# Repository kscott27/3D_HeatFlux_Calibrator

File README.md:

# 3D_HeatFlux_Calibrator
Firmware, GUI, and electronic circuit board files for a 3-dimensional, automated heat flux calibrator.

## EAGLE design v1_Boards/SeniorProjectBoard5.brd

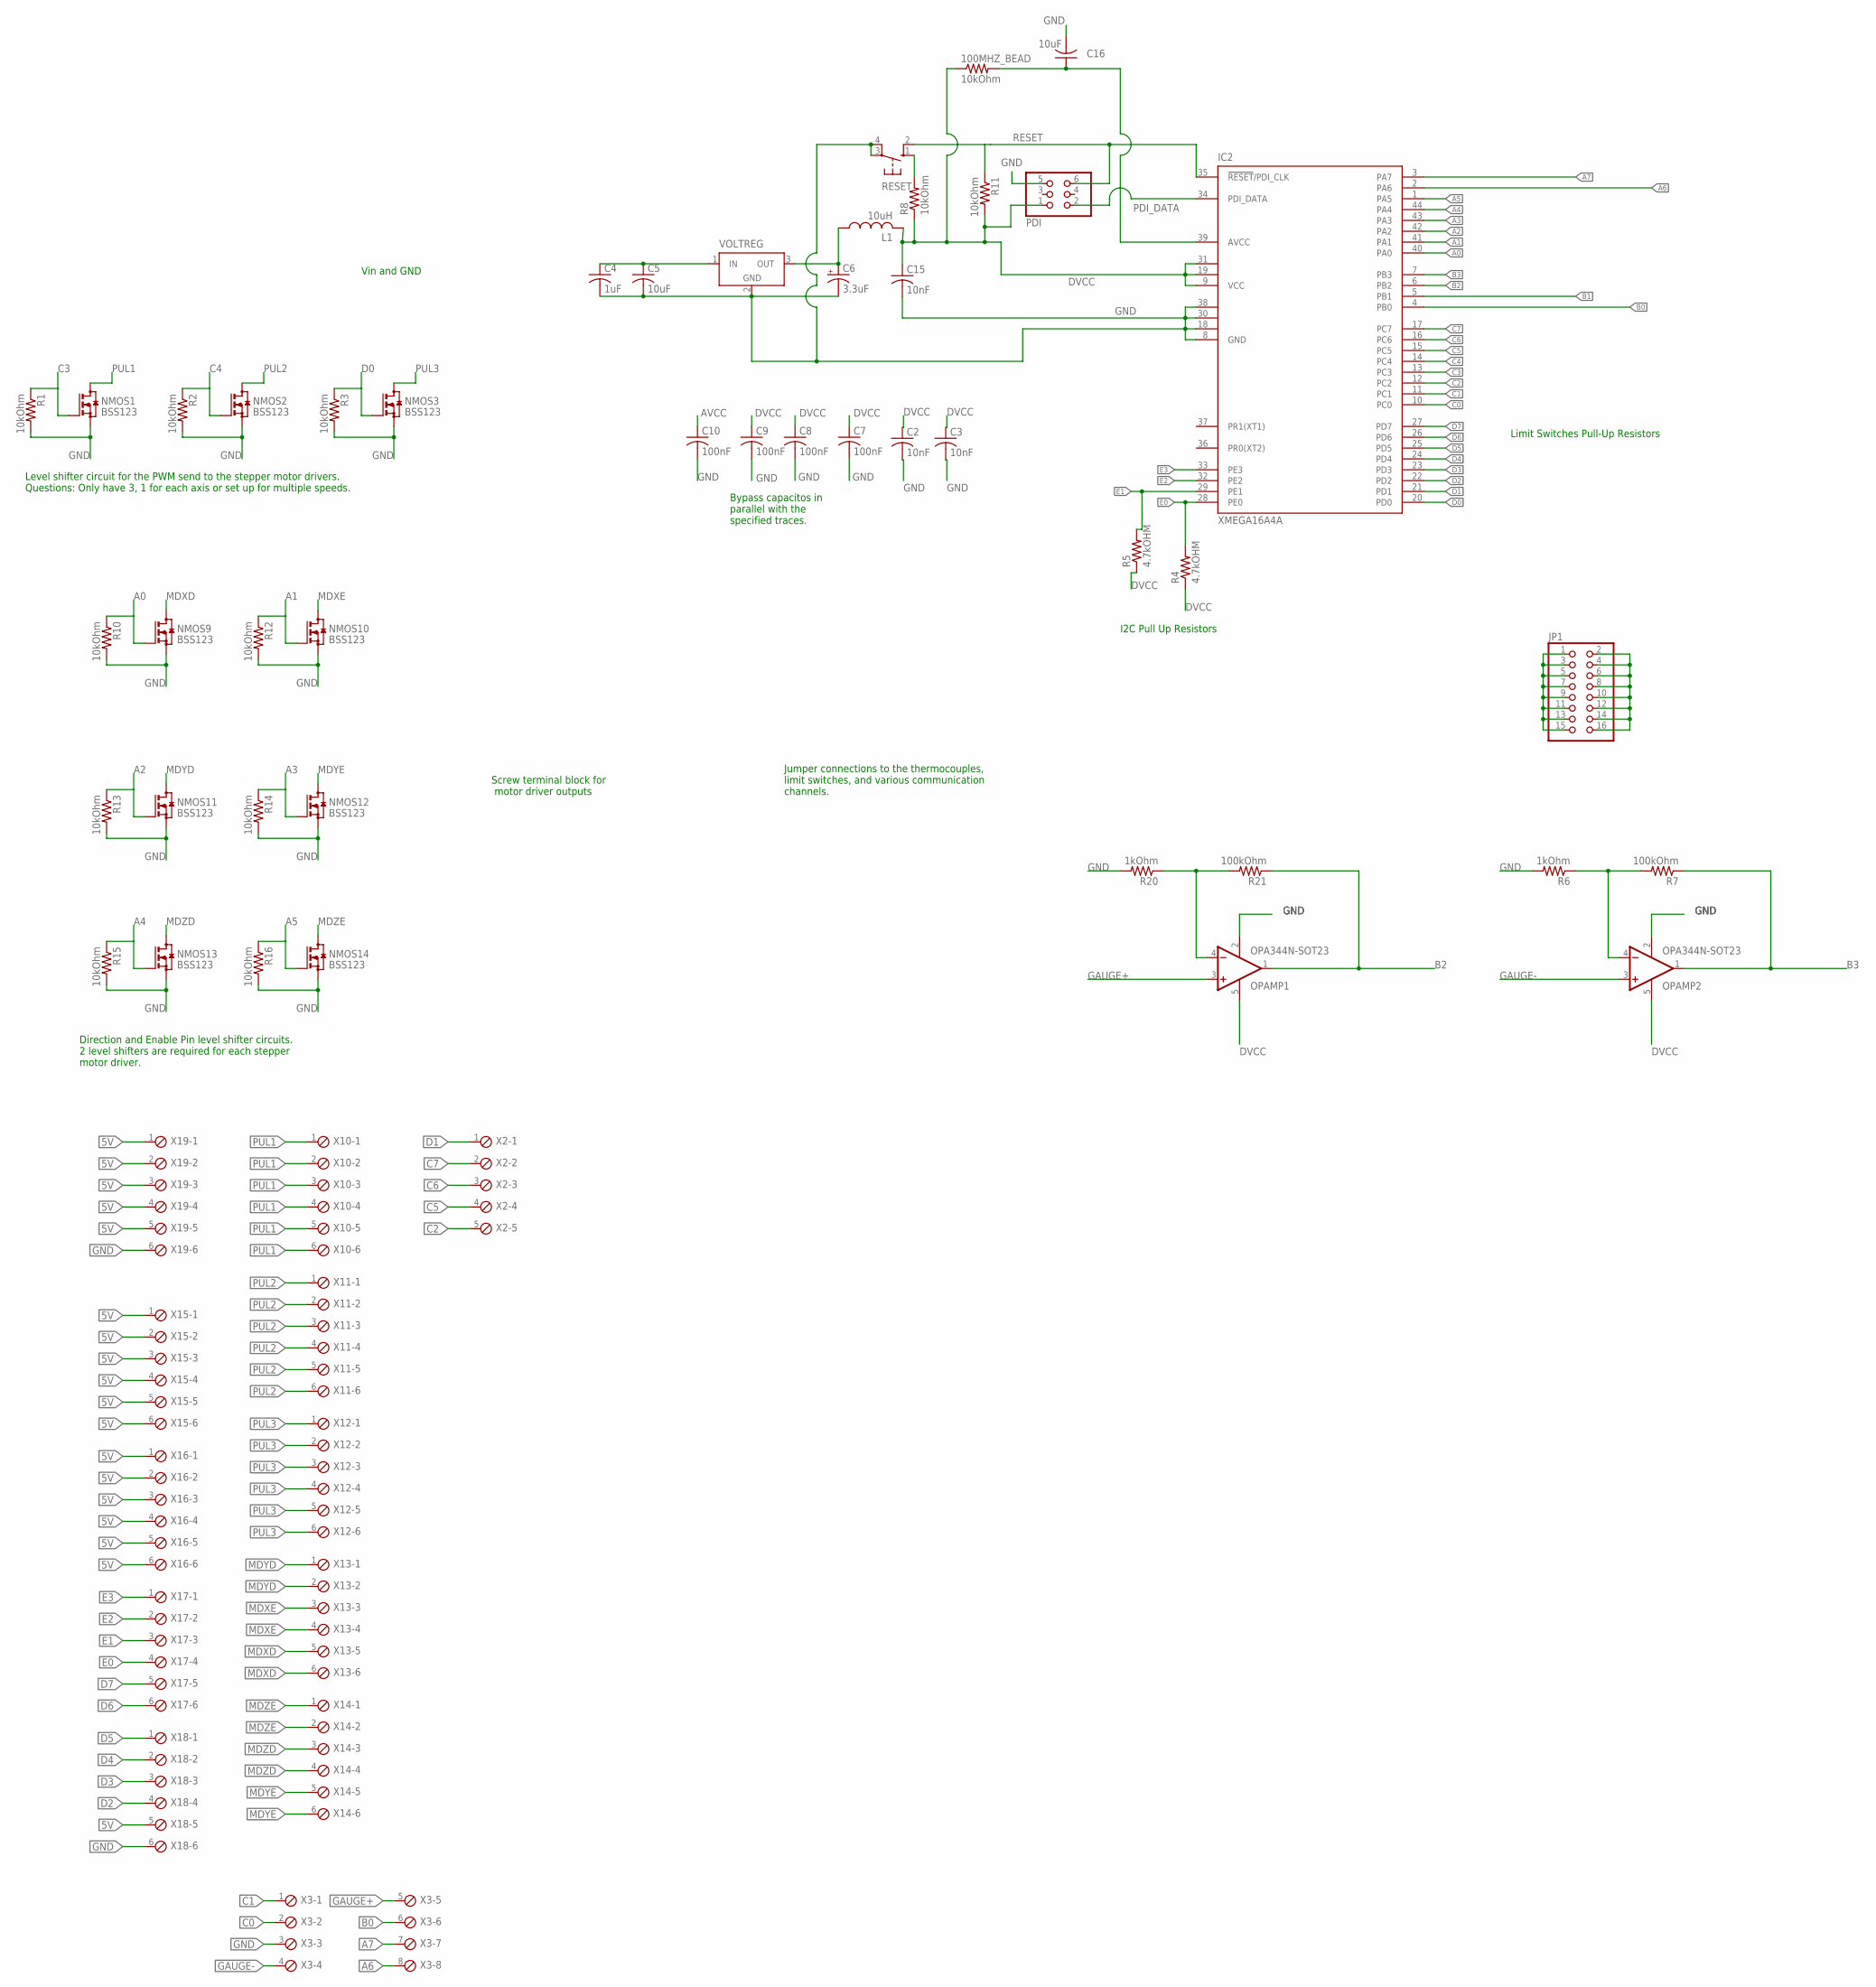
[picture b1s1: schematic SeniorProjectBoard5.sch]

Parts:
100MHZ_BEAD: 10kOhm; R0805
C2, C3, C15: 10nF; C0805
C4: 1uF; C0805
C5, C16: 10uF; C0805
C6: 3.3uF; CT3216
C7, C8, C9, C10: 100nF; C0805
IC2: XMEGA16A4A; TQFP44
JP1: PINHD-2X8; 2X08
L1: 10uH; L1812
NMOS1, NMOS2, NMOS3, NMOS9, NMOS10, NMOS11, NMOS12, NMOS13, NMOS14: BSS123; SOT23
OPAMP1, OPAMP2: OPA344N-SOT23; SOT23-5
PDI: PINHD-2X3; 2X03
R1, R2, R3, R8, R10, R11, R12, R13, R14, R15, R16: 10kOhm; R0805
R4, R5: 4.7kOHM; R0805
R6, R20: 1kOhm; R0805
R7, R21: 100kOhm; R0805
RESET: 10-XX; B3F-10XX
VOLTREG: LT1129CST5; SOT223
X2: MPT5; 5POL254
X3: MPT8; 8POL254
X10, X11, X12, X13, X14, X15, X16, X17, X18, X19: MPT6; 6POL254

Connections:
5V: C4.1, C5.1, VOLTREG.1 (IN), X15.1, X15.2, X15.3, X15.4, X15.5, X15.6, X16.1, X16.2, X16.3, X16.4, X16.5, X16.6, X18.5, X19.1, X19.2, X19.3, X19.4, X19.5
A0: IC2.40 (PA0), NMOS9.1 (G), R10.1
A1: IC2.41 (PA1), NMOS10.1 (G), R12.1
A2: IC2.42 (PA2), NMOS11.1 (G), R13.1
A3: IC2.43 (PA3), NMOS12.1 (G), R14.1
A4: IC2.44 (PA4), NMOS13.1 (G), R15.1
A5: IC2.1 (PA5), NMOS14.1 (G), R16.1
A6: IC2.2 (PA6), X3.8
A7: IC2.3 (PA7), X3.7
AVCC: 100MHZ_BEAD.2, C10.1, C16.1, IC2.39 (AVCC)
B0: IC2.4 (PB0), X3.6
B1: IC2.5 (PB1)
B2: IC2.6 (PB2), OPAMP1.1 (OUT), R21.1
B3: IC2.7 (PB3), OPAMP2.1 (OUT), R7.1
C0: IC2.10 (PC0), X3.2
C1: IC2.11 (PC1), X3.1
C2: IC2.12 (PC2), X2.5
C3: IC2.13 (PC3), NMOS1.1 (G), R1.1
C4: IC2.14 (PC4), NMOS2.1 (G), R2.1
C5: IC2.15 (PC5), X2.4
C6: IC2.16 (PC6), X2.3
C7: IC2.17 (PC7), X2.2
D0: IC2.20 (PD0), NMOS3.1 (G), R3.1
D1: IC2.21 (PD1), X2.1
D2: IC2.22 (PD2), X18.4
D3: IC2.23 (PD3), X18.3
D4: IC2.24 (PD4), X18.2
D5: IC2.25 (PD5), X18.1
D6: IC2.26 (PD6), X17.6
D7: IC2.27 (PD7), X17.5
DVCC: 100MHZ_BEAD.1, C2.1, C3.1, C7.1, C8.1, C9.1, C15.1, IC2.9 (VCC), IC2.19 (VCC1), IC2.31 (VCC2), JP1.1, JP1.3, JP1.5, JP1.7, JP1.9, JP1.11, JP1.13, JP1.15, L1.2, OPAMP1.5 (V+), OPAMP2.5 (V+), PDI.1, R4.1, R5.1, R8.1, R11.2
E0: IC2.28 (PE0), R4.2, X17.4
E1: IC2.29 (PE1), R5.2, X17.3
E2: IC2.32 (PE2), X17.2
E3: IC2.33 (PE3), X17.1
GAUGE+: OPAMP1.3 (+IN), X3.5
GAUGE-: OPAMP2.3 (+IN), X3.4
GND: C2.2, C3.2, C4.2, C5.2, C6.-, C7.2, C8.2, C9.2, C10.2, C15.2, C16.2, IC2.8 (GND), IC2.18 (GND1), IC2.30 (GND2), IC2.38 (GND3), JP1.2, JP1.4, JP1.6, JP1.8, JP1.10, JP1.12, JP1.14, JP1.16, NMOS1.2 (S), NMOS2.2 (S), NMOS3.2 (S), NMOS9.2 (S), NMOS10.2 (S), NMOS11.2 (S), NMOS12.2 (S), NMOS13.2 (S), NMOS14.2 (S), OPAMP1.2 (V-), OPAMP2.2 (V-), PDI.5, R1.2, R2.2, R3.2, R6.2, R10.2, R12.2, R13.2, R14.2, R15.2, R16.2, R20.2, RESET.3, RESET.4 (P1), VOLTREG.2 (GND), VOLTREG.4 (GND), X3.3, X18.6, X19.6
MDXD: NMOS9.3 (D), X13.5, X13.6
MDXE: NMOS10.3 (D), X13.3, X13.4
MDYD: NMOS11.3 (D), X13.1, X13.2
MDYE: NMOS12.3 (D), X14.5, X14.6
MDZD: NMOS13.3 (D), X14.3, X14.4
MDZE: NMOS14.3 (D), X14.1, X14.2
unnamed: OPAMP2.4 (-IN), R6.1, R7.2
unnamed: OPAMP1.4 (-IN), R20.1, R21.2
PDI_DATA: IC2.34 (PDI_DATA), PDI.2
PUL1: NMOS1.3 (D), X10.1, X10.2, X10.3, X10.4, X10.5, X10.6
PUL2: NMOS2.3 (D), X11.1, X11.2, X11.3, X11.4, X11.5, X11.6
PUL3: NMOS3.3 (D), X12.1, X12.2, X12.3, X12.4, X12.5, X12.6
RESET: IC2.35 (!RESET!/PDI_CLK), PDI.6, R11.1, RESET.2 (S1)
SW_PULLUP: R8.2, RESET.1 (S)
V_REG_OUT: C6.+, L1.1, VOLTREG.3 (OUT)

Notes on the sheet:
Bypass capacitos in parallel with the specified traces.
Level shifter circuit for the PWM send to the stepper motor drivers. Questions: Only have 3, 1 for each axis or set up for multiple speeds.
Direction and Enable Pin level shifter circuits. 2 level shifters are required for each stepper motor driver.
Limit Switches Pull-Up Resistors
Jumper connections to the thermocouples, limit switches, and various communication channels.
Screw terminal block for motor driver outputs
I2C Pull Up Resistors
Vin and GND

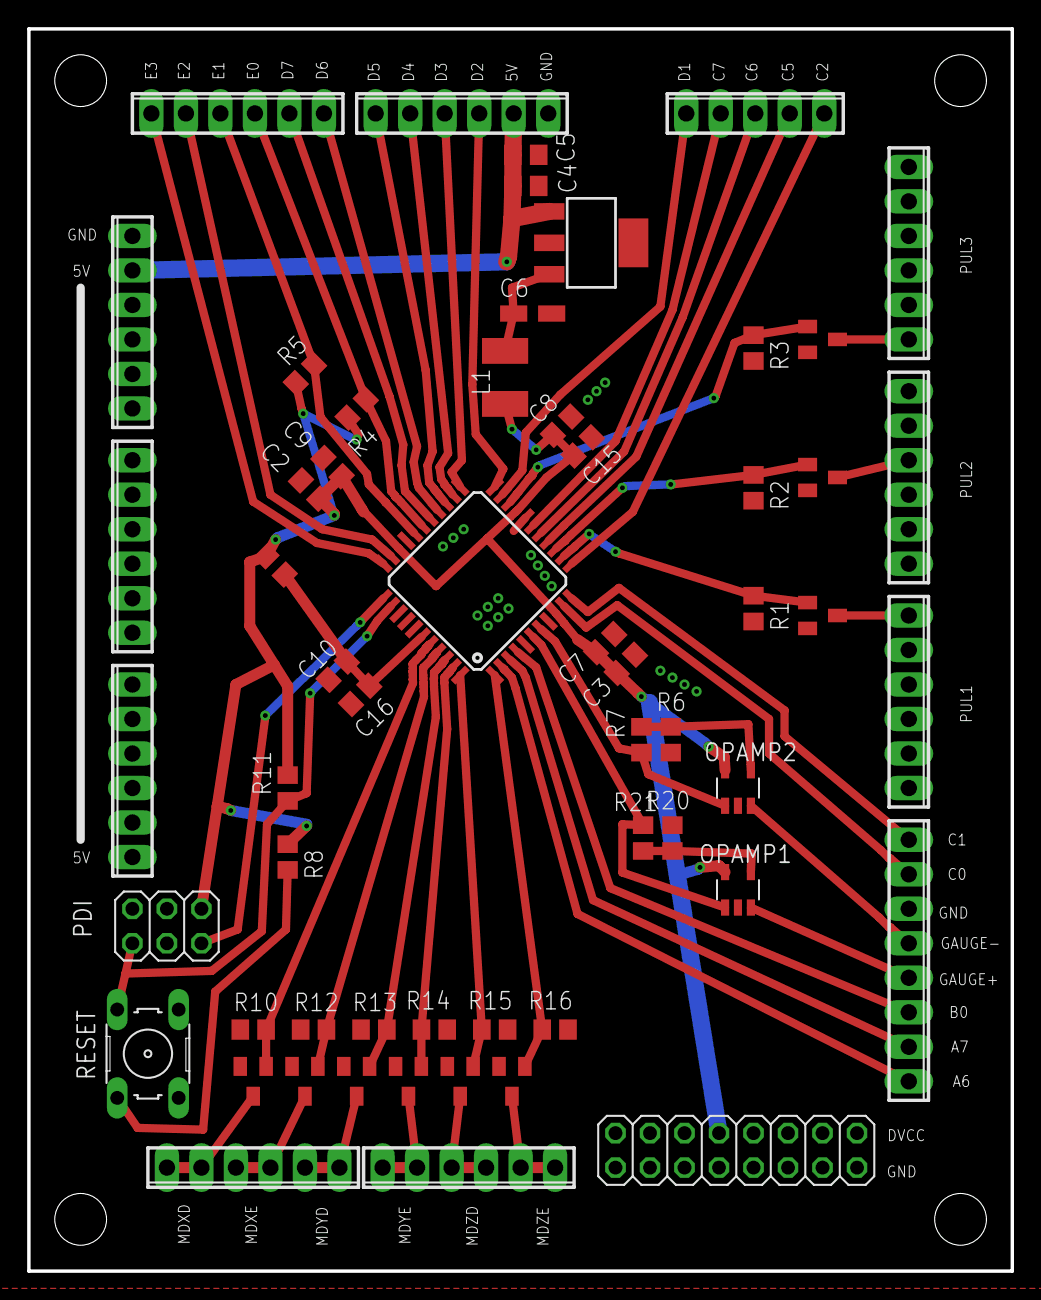
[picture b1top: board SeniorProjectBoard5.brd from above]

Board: 2 copper layers, 72.4 x 91.4 mm, 58 parts (0 on the bottom side), 52 nets.

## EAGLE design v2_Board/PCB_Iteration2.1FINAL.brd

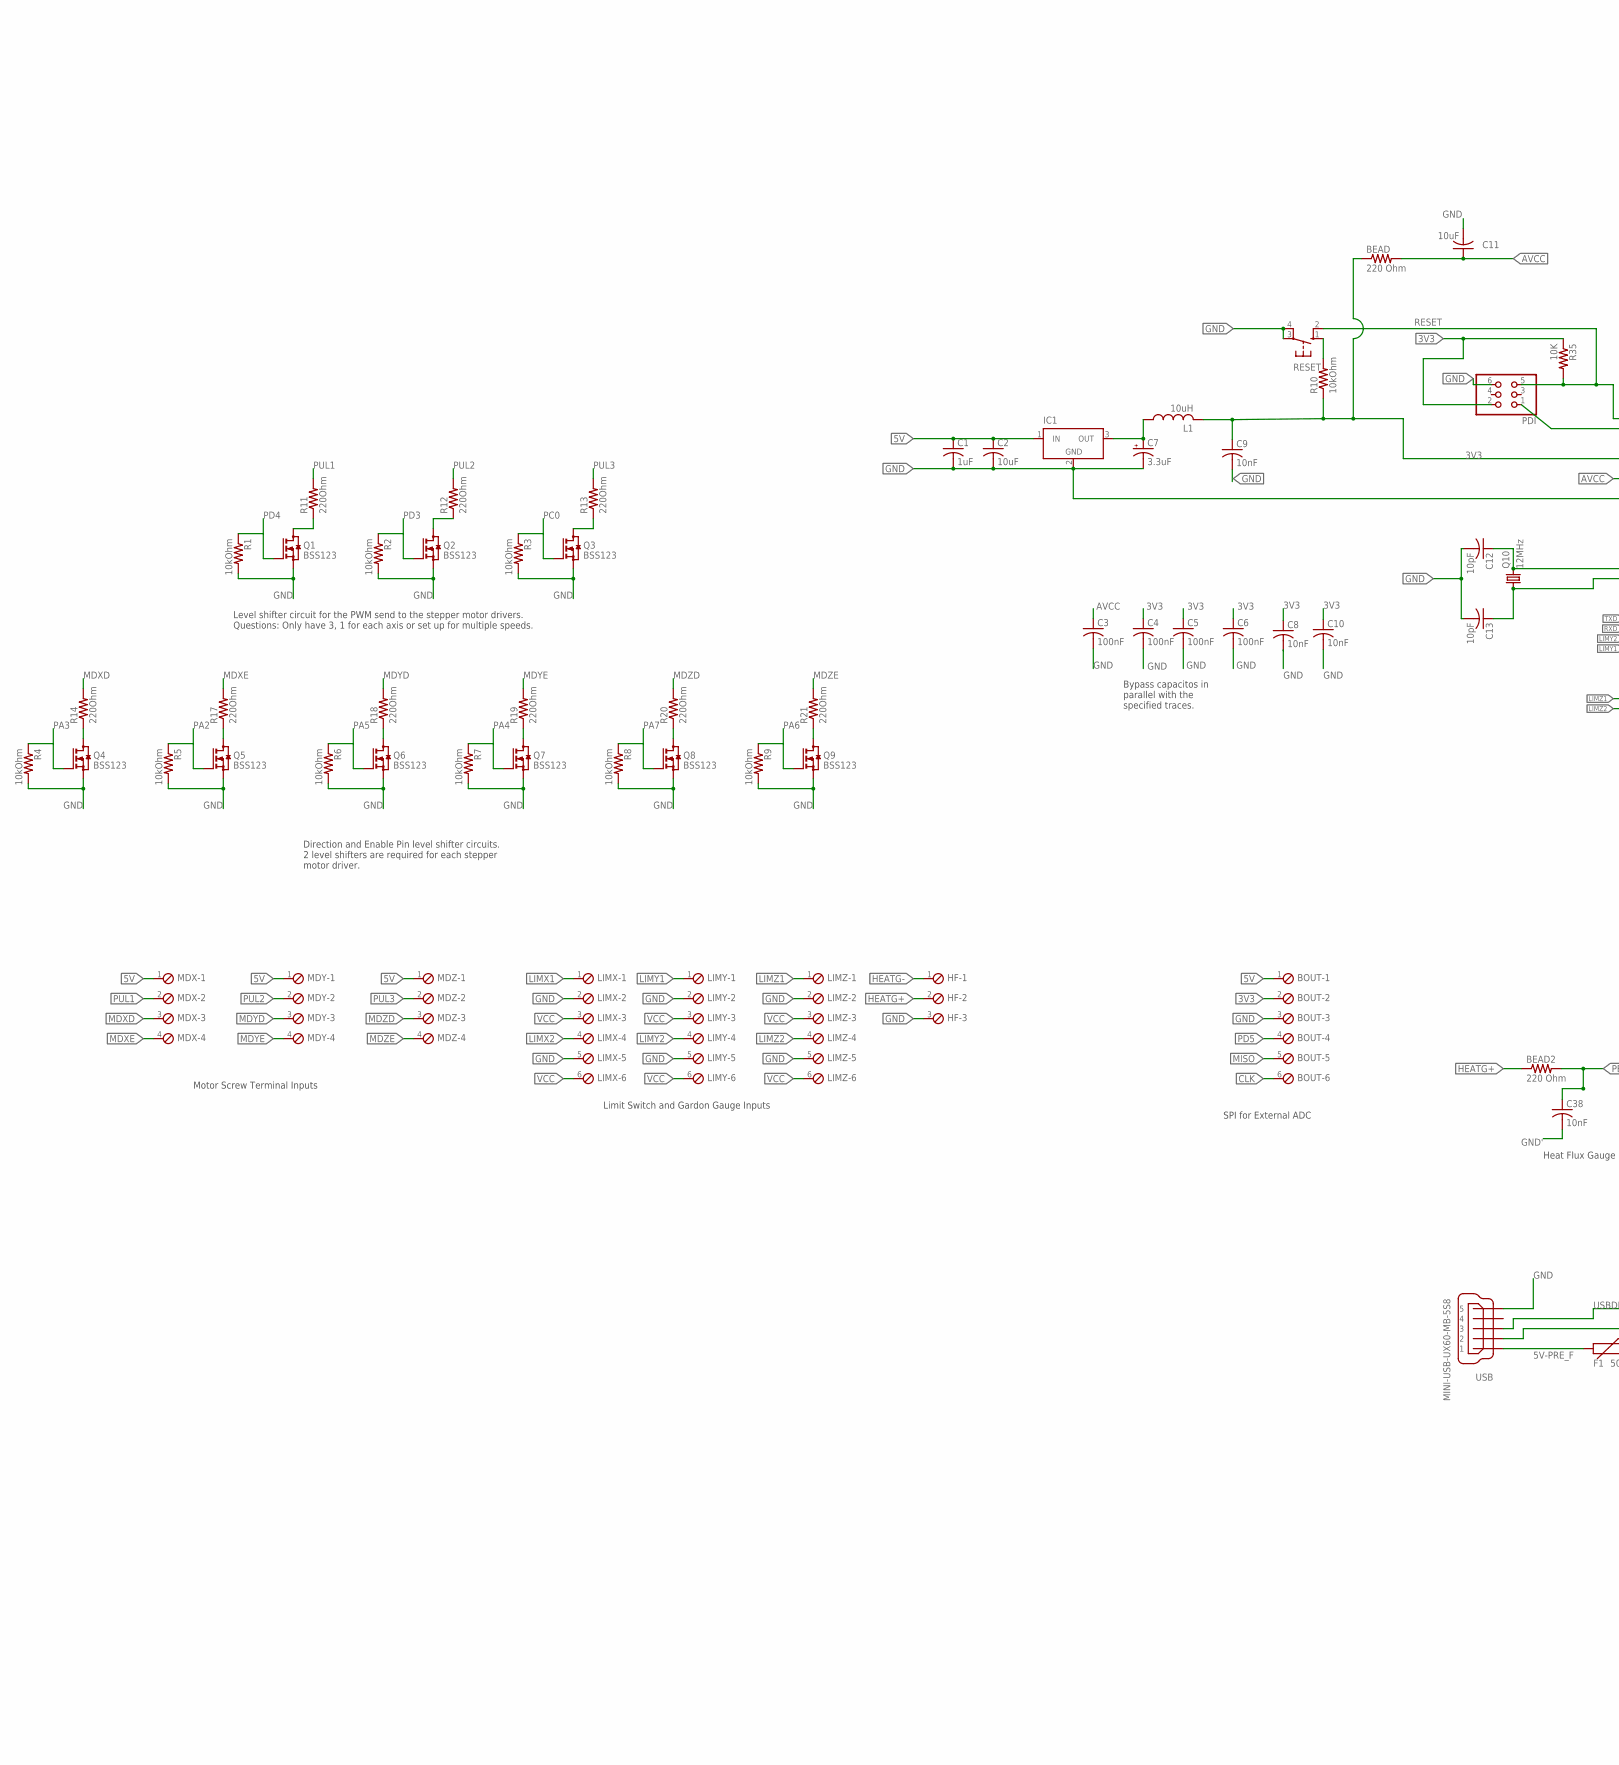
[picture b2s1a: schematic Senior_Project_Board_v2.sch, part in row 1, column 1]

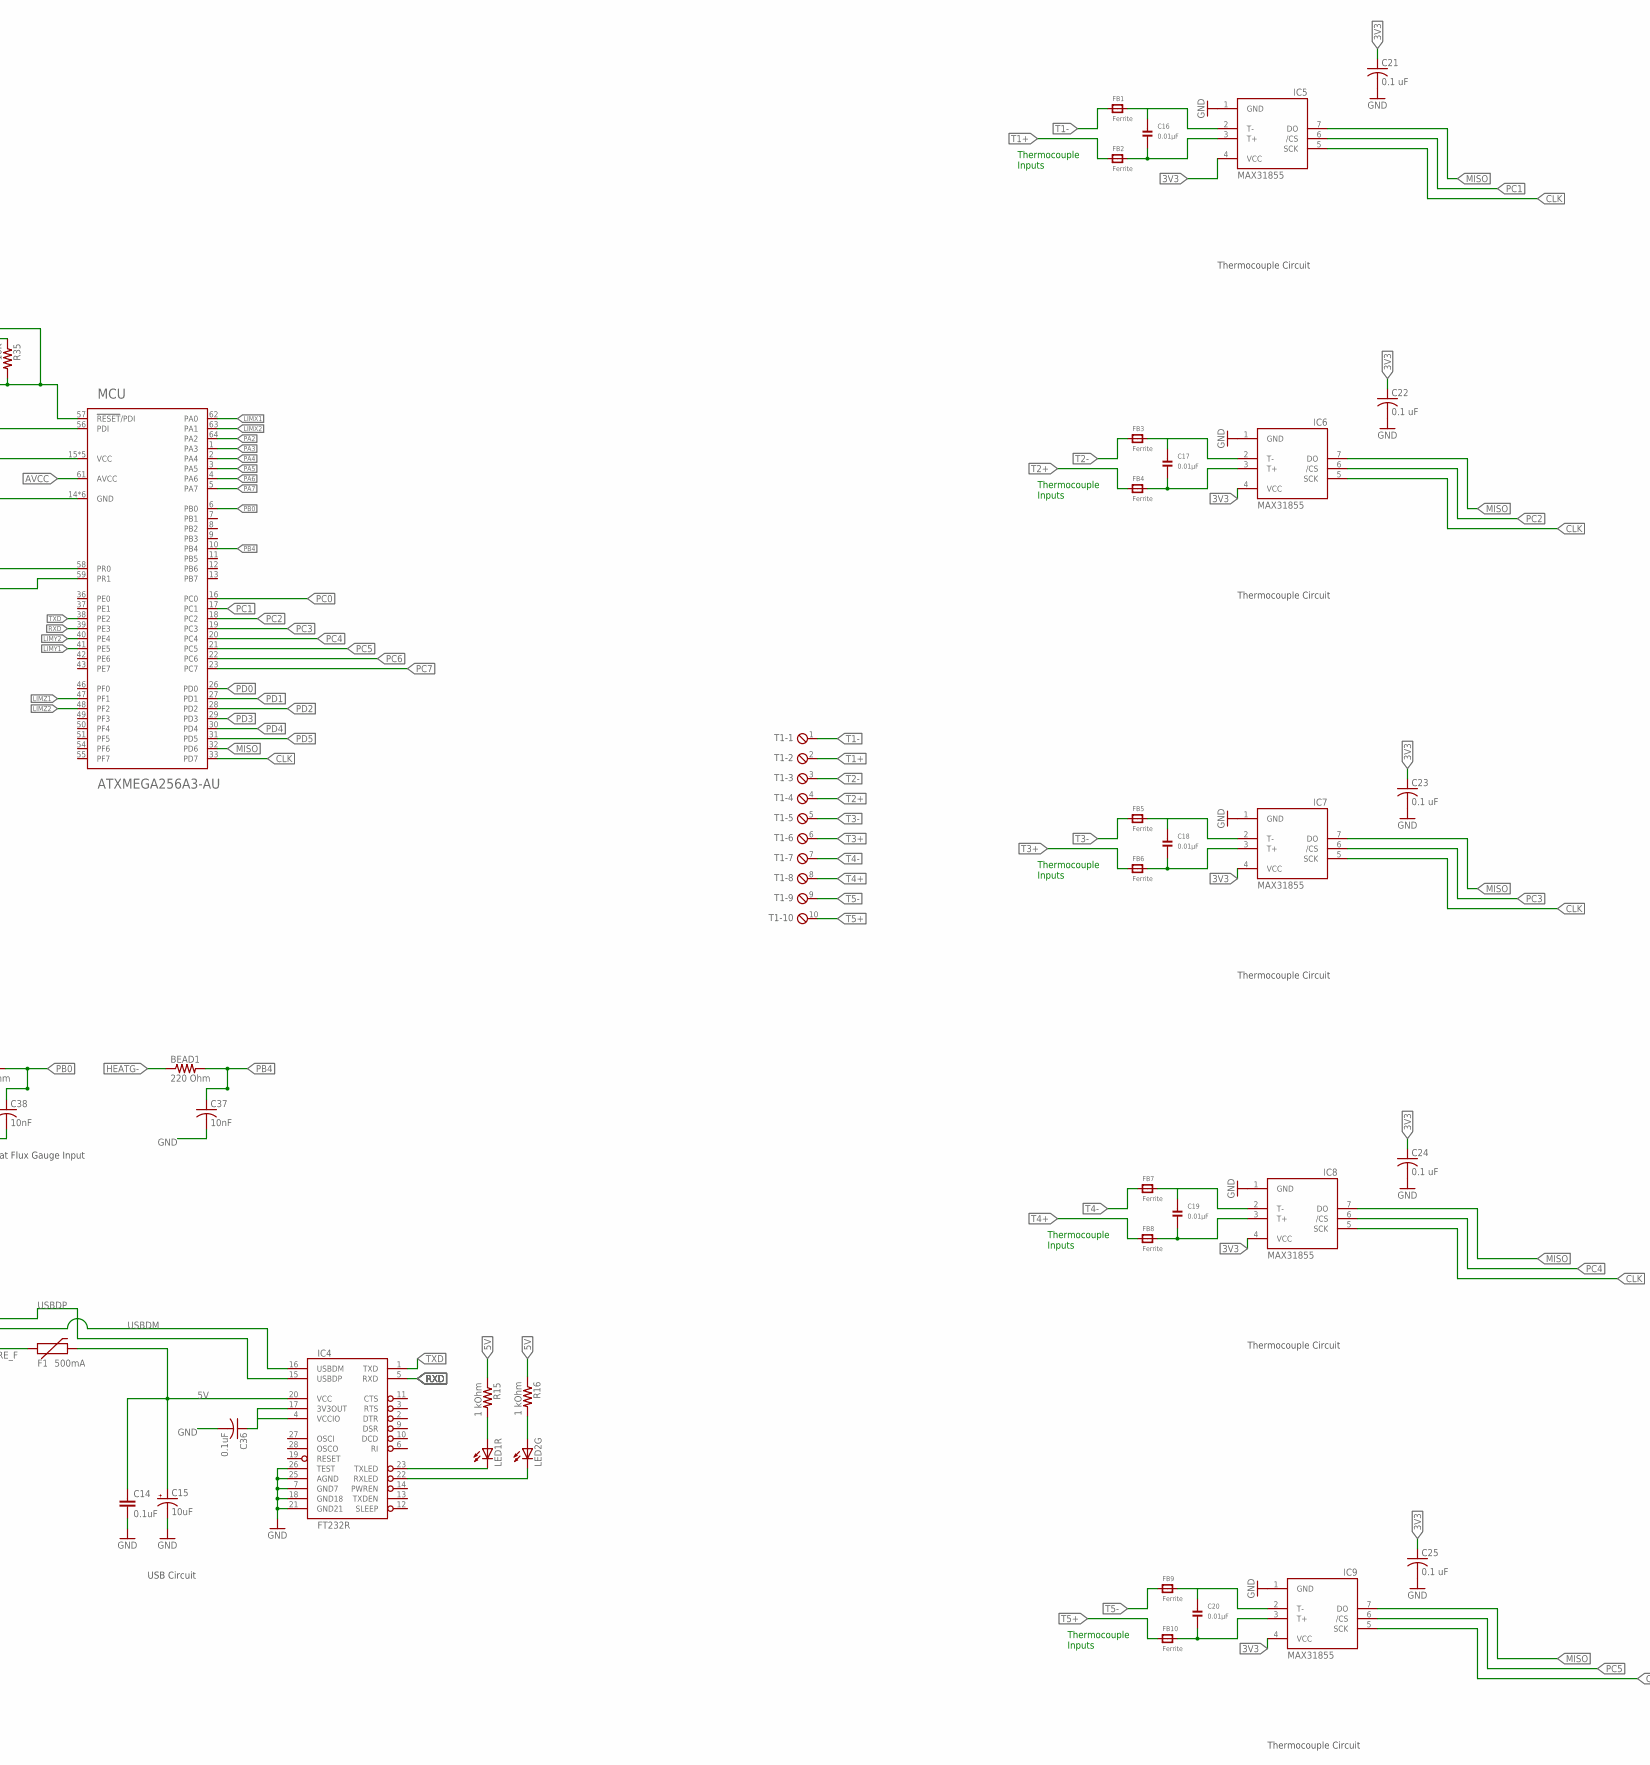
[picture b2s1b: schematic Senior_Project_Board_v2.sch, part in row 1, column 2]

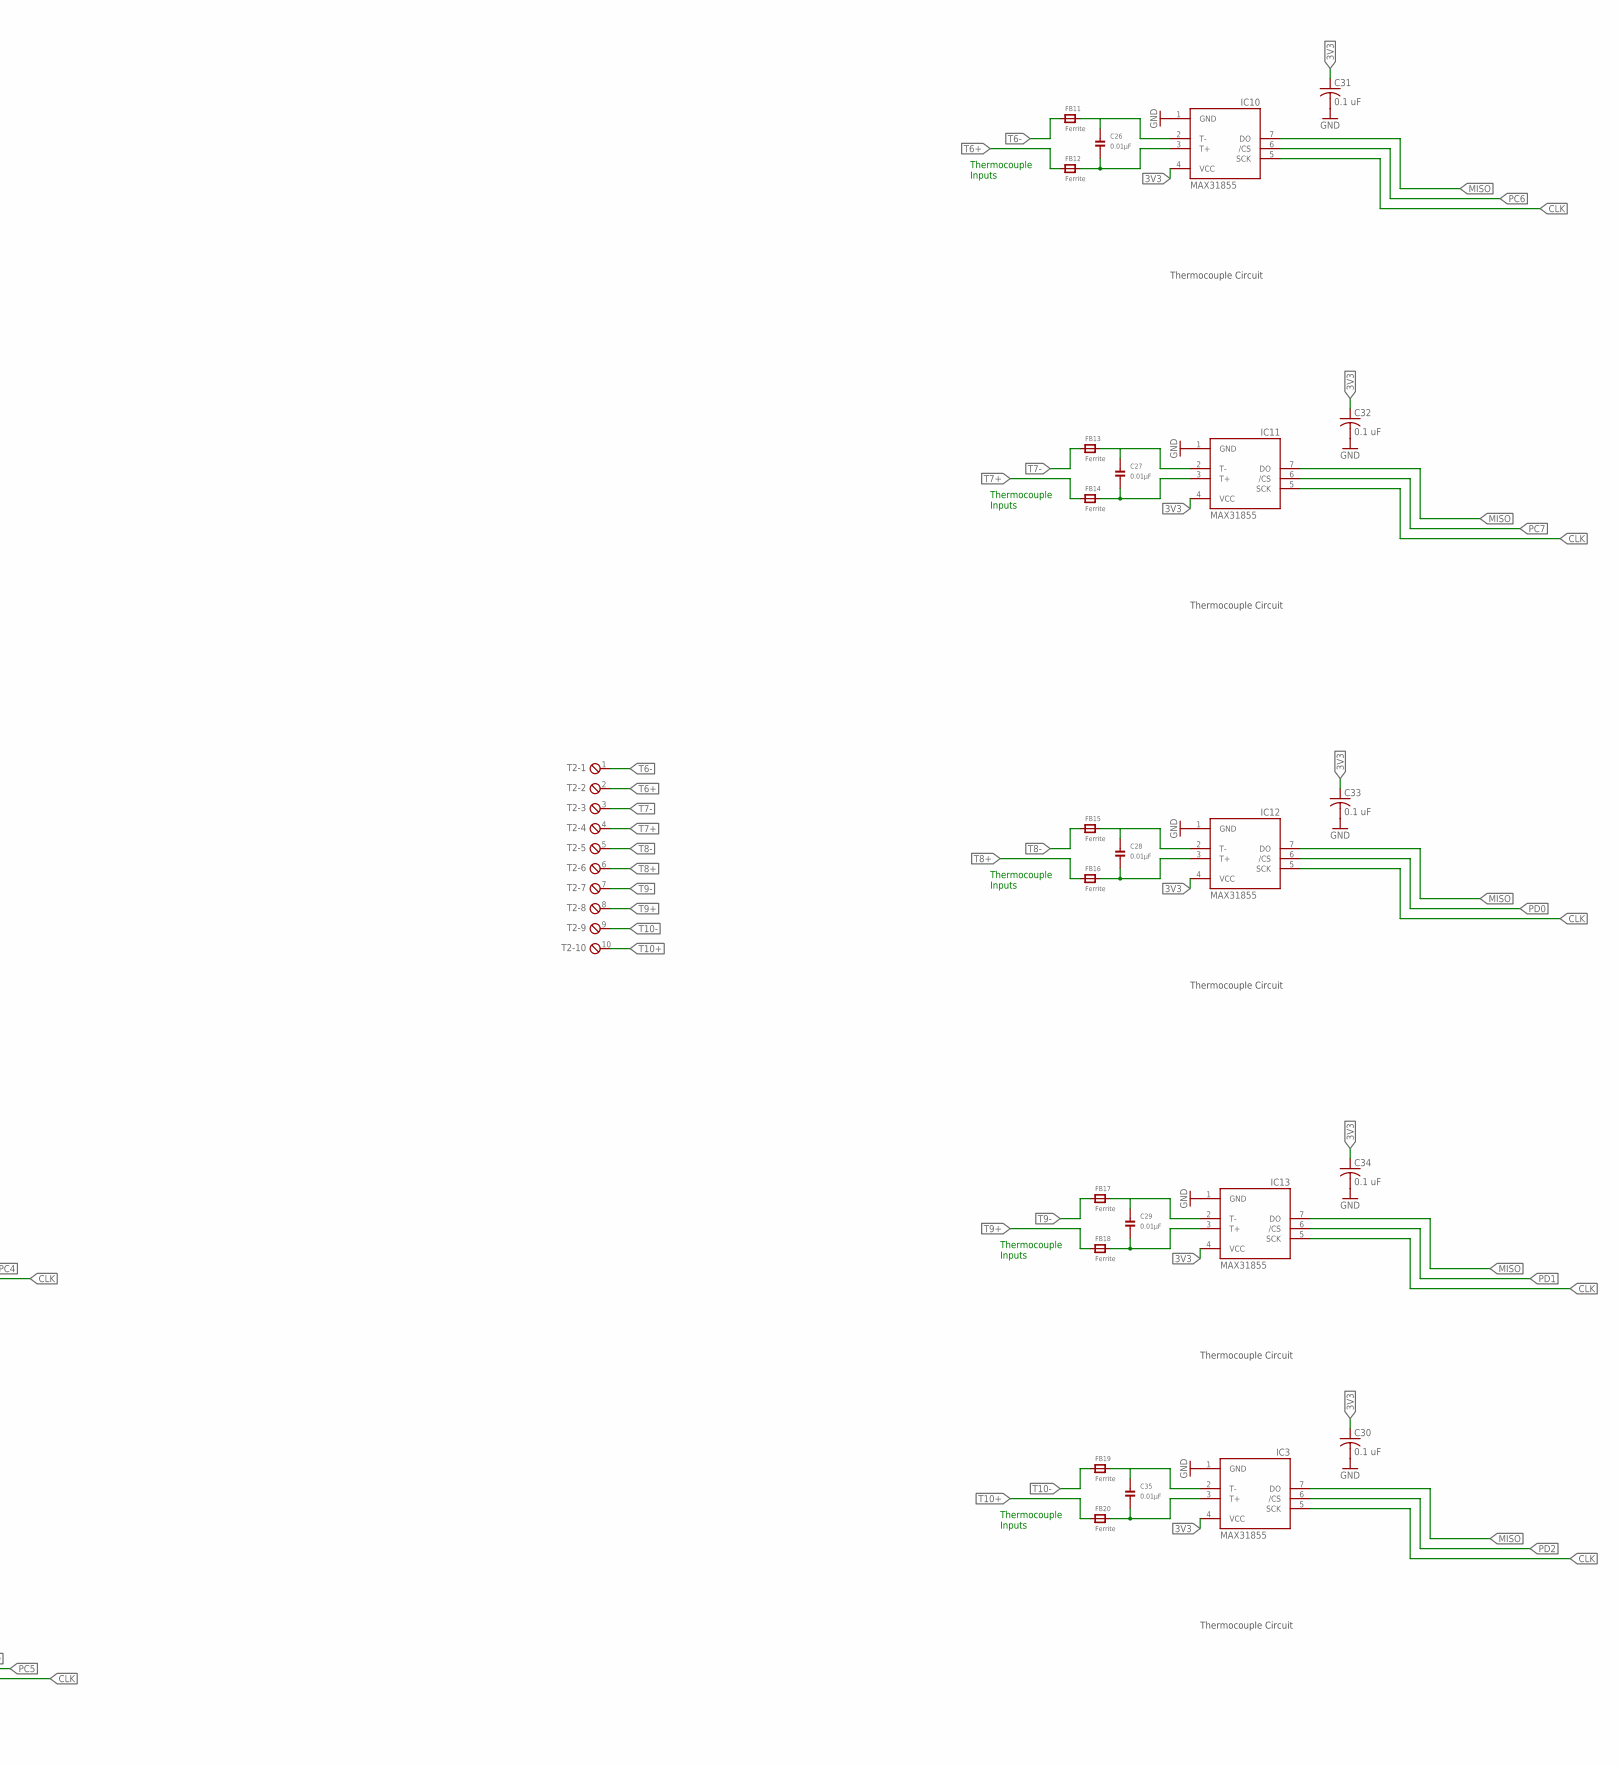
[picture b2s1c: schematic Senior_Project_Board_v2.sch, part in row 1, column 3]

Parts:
BEAD, BEAD1, BEAD2: 220 Ohm; R0805
BOUT: MPT6; 6POL254
C1: 1uF; C0805
C2, C11: 10uF; C0805
C3, C4, C5, C6: 100nF; C0805
C7: 3.3uF; CT3216
C8, C9, C10, C37, C38: 10nF; C0805
C12, C13: 10pF; C0805
C14: 0.1uF; 0603-CAP
C15: 10uF; EIA3216
C16, C17, C18, C19, C20, C26, C27, C28, C29, C35: 0.01µF; _0805
C21, C22, C23, C24, C25, C30, C31, C32, C33, C34: 0.1 uF; C0805K
C36: 0.1uF; C0805
F1: 500mA; PTC-1206
FB1, FB2, FB3, FB4, FB5, FB6, FB7, FB8, FB9, FB10, FB11, FB12, FB13, FB14, FB15, FB16, FB17, FB18, FB19, FB20: Ferrite; _0805
HF: MPT3; 3POL254
IC1: LT1129CST5; SOT223
IC3, IC5, IC6, IC7, IC8, IC9, IC10, IC11, IC12, IC13: MAX31855; SO08
IC4: FT232R; SSOP28DB
L1: 10uH; L1812
LED1R, LED2G: LED_E; LED_1206
LIMX: MPT6; 6POL254
LIMY: MPT6; 6POL254
LIMZ: MPT6; 6POL254
MCU: ATXMEGA256A3-AU; TQFP-64A-64
MDX: MPT4; 4POL254
MDY: MPT4; 4POL254
MDZ: MPT4; 4POL254
PDI: PINHD-2X3; 2X03
Q1, Q2, Q3, Q4, Q5, Q6, Q7, Q8, Q9: BSS123; SOT23
Q10: 12MHz; HC49/S
R1, R2, R3, R4, R5, R6, R7, R8, R9, R10: 10kOhm; R0805
R11, R12, R13, R14, R17, R18, R19, R20, R21: 220Ohm; R0805
R15, R16: 1 kOhm; R0805
R35: 10K; R0805
RESET: 10-XX; B3F-10XX
T1, T2: MPT10; 10POL254
USB: MINI-USB-UX60-MB-5S8; UX60-MB-5S8

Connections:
3V3: BEAD.1, BOUT.2, C4.1, C5.1, C6.1, C8.1, C9.1, C10.1, C21.1, C22.1, C23.1, C24.1, C25.1, C30.1, C31.1, C32.1, C33.1, C34.1, IC3.4 (VCC), IC5.4 (VCC), IC6.4 (VCC), IC7.4 (VCC), IC8.4 (VCC), IC9.4 (VCC), IC10.4 (VCC), IC11.4 (VCC), IC12.4 (VCC), IC13.4 (VCC), L1.2, MCU.15 (VCC), MCU.25 (VCC), MCU.35 (VCC), MCU.45 (VCC), MCU.53 (VCC), PDI.2, R10.1, R35.1
5V: BOUT.1, C1.1, C2.1, C14.1, C15.A (+), F1.2, IC1.1 (IN), IC4.20 (VCC), MDX.1, MDY.1, MDZ.1, R15.1, R16.1
5V-PRE_F: F1.1, USB.1
AVCC: BEAD.2, C3.1, C11.1, MCU.61 (AVCC)
CLK: BOUT.6, IC3.5 (SCK), IC5.5 (SCK), IC6.5 (SCK), IC7.5 (SCK), IC8.5 (SCK), IC9.5 (SCK), IC10.5 (SCK), IC11.5 (SCK), IC12.5 (SCK), IC13.5 (SCK), MCU.33 (PD7)
GND: BOUT.3, C1.2, C2.2, C3.2, C4.2, C5.2, C6.2, C7.-, C8.2, C9.2, C10.2, C11.2, C12.2, C13.2, C14.2, C15.C (-), C21.2, C22.2, C23.2, C24.2, C25.2, C30.2, C31.2, C32.2, C33.2, C34.2, C36.2, C37.2, HF.3, IC1.2 (GND), IC1.4 (GND), IC3.1 (GND), IC4.7 (GND7), IC4.18 (GND18), IC4.21 (GND21), IC4.25 (AGND), IC4.26 (TEST), IC5.1 (GND), IC6.1 (GND), IC7.1 (GND), IC8.1 (GND), IC9.1 (GND), IC10.1 (GND), IC11.1 (GND), IC12.1 (GND), IC13.1 (GND), LIMX.2, LIMX.5, LIMY.2, LIMY.5, LIMZ.2, LIMZ.5, MCU.14 (GND), MCU.24 (GND), MCU.34 (GND), MCU.44 (GND), MCU.52 (GND), MCU.60 (GND), PDI.6, Q1.2 (S), Q2.2 (S), Q3.2 (S), Q4.2 (S), Q5.2 (S), Q6.2 (S), Q7.2 (S), Q8.2 (S), Q9.2 (S), R1.2, R2.2, R3.2, R4.2, R5.2, R6.2, R7.2, R8.2, R9.2, RESET.3, RESET.4 (P1), USB.5
GND': C38.2
HEATG+: BEAD2.1, HF.2
HEATG-: BEAD1.1, HF.1
LIMX1: LIMX.1, MCU.62 (PA0)
LIMX2: LIMX.4, MCU.63 (PA1)
LIMY1: LIMY.1, MCU.41 (PE5)
LIMY2: LIMY.4, MCU.40 (PE4)
LIMZ1: LIMZ.1, MCU.47 (PF1)
LIMZ2: LIMZ.4, MCU.48 (PF2)
MDXD: MDX.3, R14.2
MDXE: MDX.4, R17.2
MDYD: MDY.3, R18.2
MDYE: MDY.4, R19.2
MDZD: MDZ.3, R20.2
MDZE: MDZ.4, R21.2
MISO: BOUT.5, IC3.7 (DO), IC5.7 (DO), IC6.7 (DO), IC7.7 (DO), IC8.7 (DO), IC9.7 (DO), IC10.7 (DO), IC11.7 (DO), IC12.7 (DO), IC13.7 (DO), MCU.32 (PD6)
unnamed: Q5.3 (D), R17.1
unnamed: C17.1, FB3.2, IC6.2 (T-)
unnamed: C35.1, FB19.2, IC3.2 (T-)
unnamed: C16.1, FB1.2, IC5.2 (T-)
unnamed: MCU.56 (PDI), PDI.1
unnamed: C16.2, FB2.2, IC5.3 (T+)
unnamed: LED1R.A, R15.2
unnamed: C36.1, IC4.4 (VCCIO), IC4.17 (3V3OUT)
unnamed: IC4.23 (TXLED), LED1R.C
unnamed: LED2G.A, R16.2
unnamed: Q8.3 (D), R20.1
unnamed: IC4.22 (RXLED), LED2G.C
unnamed: Q9.3 (D), R21.1
unnamed: Q6.3 (D), R18.1
unnamed: C35.2, FB20.2, IC3.3 (T+)
unnamed: Q2.3 (D), R12.1
unnamed: C17.2, FB4.2, IC6.3 (T+)
unnamed: Q7.3 (D), R19.1
unnamed: C18.1, FB5.2, IC7.2 (T-)
unnamed: Q1.3 (D), R11.1
unnamed: C18.2, FB6.2, IC7.3 (T+)
unnamed: Q4.3 (D), R14.1
unnamed: C19.1, FB7.2, IC8.2 (T-)
unnamed: C19.2, FB8.2, IC8.3 (T+)
unnamed: Q3.3 (D), R13.1
unnamed: C20.1, FB9.2, IC9.2 (T-)
unnamed: C20.2, FB10.2, IC9.3 (T+)
unnamed: C26.1, FB11.2, IC10.2 (T-)
unnamed: C26.2, FB12.2, IC10.3 (T+)
unnamed: C27.1, FB13.2, IC11.2 (T-)
unnamed: C27.2, FB14.2, IC11.3 (T+)
unnamed: C28.1, FB15.2, IC12.2 (T-)
unnamed: C28.2, FB16.2, IC12.3 (T+)
unnamed: C29.1, FB17.2, IC13.2 (T-)
unnamed: C29.2, FB18.2, IC13.3 (T+)
PA2: MCU.64 (PA2), Q5.1 (G), R5.1
PA3: MCU.1 (PA3), Q4.1 (G), R4.1
PA4: MCU.2 (PA4), Q7.1 (G), R7.1
PA5: MCU.3 (PA5), Q6.1 (G), R6.1
PA6: MCU.4 (PA6), Q9.1 (G), R9.1
PA7: MCU.5 (PA7), Q8.1 (G), R8.1
PB0: BEAD2.2, C38.1, MCU.6 (PB0)
PB4: BEAD1.2, C37.1, MCU.10 (PB4)
PC0: MCU.16 (PC0), Q3.1 (G), R3.1
PC1: IC5.6 (/CS), MCU.17 (PC1)
PC2: IC6.6 (/CS), MCU.18 (PC2)
PC3: IC7.6 (/CS), MCU.19 (PC3)
PC4: IC8.6 (/CS), MCU.20 (PC4)
PC5: IC9.6 (/CS), MCU.21 (PC5)
PC6: IC10.6 (/CS), MCU.22 (PC6)
PC7: IC11.6 (/CS), MCU.23 (PC7)
PD0: IC12.6 (/CS), MCU.26 (PD0)
PD1: IC13.6 (/CS), MCU.27 (PD1)
PD2: IC3.6 (/CS), MCU.28 (PD2)
PD3: MCU.29 (PD3), Q2.1 (G), R2.1
PD4: MCU.30 (PD4), Q1.1 (G), R1.1
PD5: BOUT.4, MCU.31 (PD5)
PUL1: MDX.2, R11.2
PUL2: MDY.2, R12.2
PUL3: MDZ.2, R13.2
RESET: MCU.57 (!RESET!/PDI), PDI.5, R35.2, RESET.2 (S1)
RXD: IC4.5 (RXD), MCU.39 (PE3)
SW_PULLUP: R10.2, RESET.1 (S)
T1+: FB2.1, T1.2
T1-: FB1.1, T1.1
T2+: FB4.1, T1.4
T2-: FB3.1, T1.3
T3+: FB6.1, T1.6
T3-: FB5.1, T1.5
T4+: FB8.1, T1.8
T4-: FB7.1, T1.7
T5+: FB10.1, T1.10
T5-: FB9.1, T1.9
T6+: FB12.1, T2.2
T6-: FB11.1, T2.1
T7+: FB14.1, T2.4
T7-: FB13.1, T2.3
T8+: FB16.1, T2.6
T8-: FB15.1, T2.5
T9+: FB18.1, T2.8
T9-: FB17.1, T2.7
T10+: FB20.1, T2.10
T10-: FB19.1, T2.9
TXD: IC4.1 (TXD), MCU.38 (PE2)
USBDM: IC4.16 (USBDM), USB.2
USBDP: IC4.15 (USBDP), USB.3
VCC: LIMX.3, LIMX.6, LIMY.3, LIMY.6, LIMZ.3, LIMZ.6
V_REG_OUT: C7.+, IC1.3 (OUT), L1.1
XT1: C12.1, MCU.58 (PR0), Q10.2
XT2: C13.1, MCU.59 (PR1), Q10.1

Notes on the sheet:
Bypass capacitos in parallel with the specified traces.
Level shifter circuit for the PWM send to the stepper motor drivers. Questions: Only have 3, 1 for each axis or set up for multiple speeds.
Direction and Enable Pin level shifter circuits. 2 level shifters are required for each stepper motor driver.
Thermocouple Inputs
Thermocouple Circuit
USB Circuit
Motor Screw Terminal Inputs
Limit Switch and Gardon Gauge Inputs
Heat Flux Gauge Input
SPI for External ADC

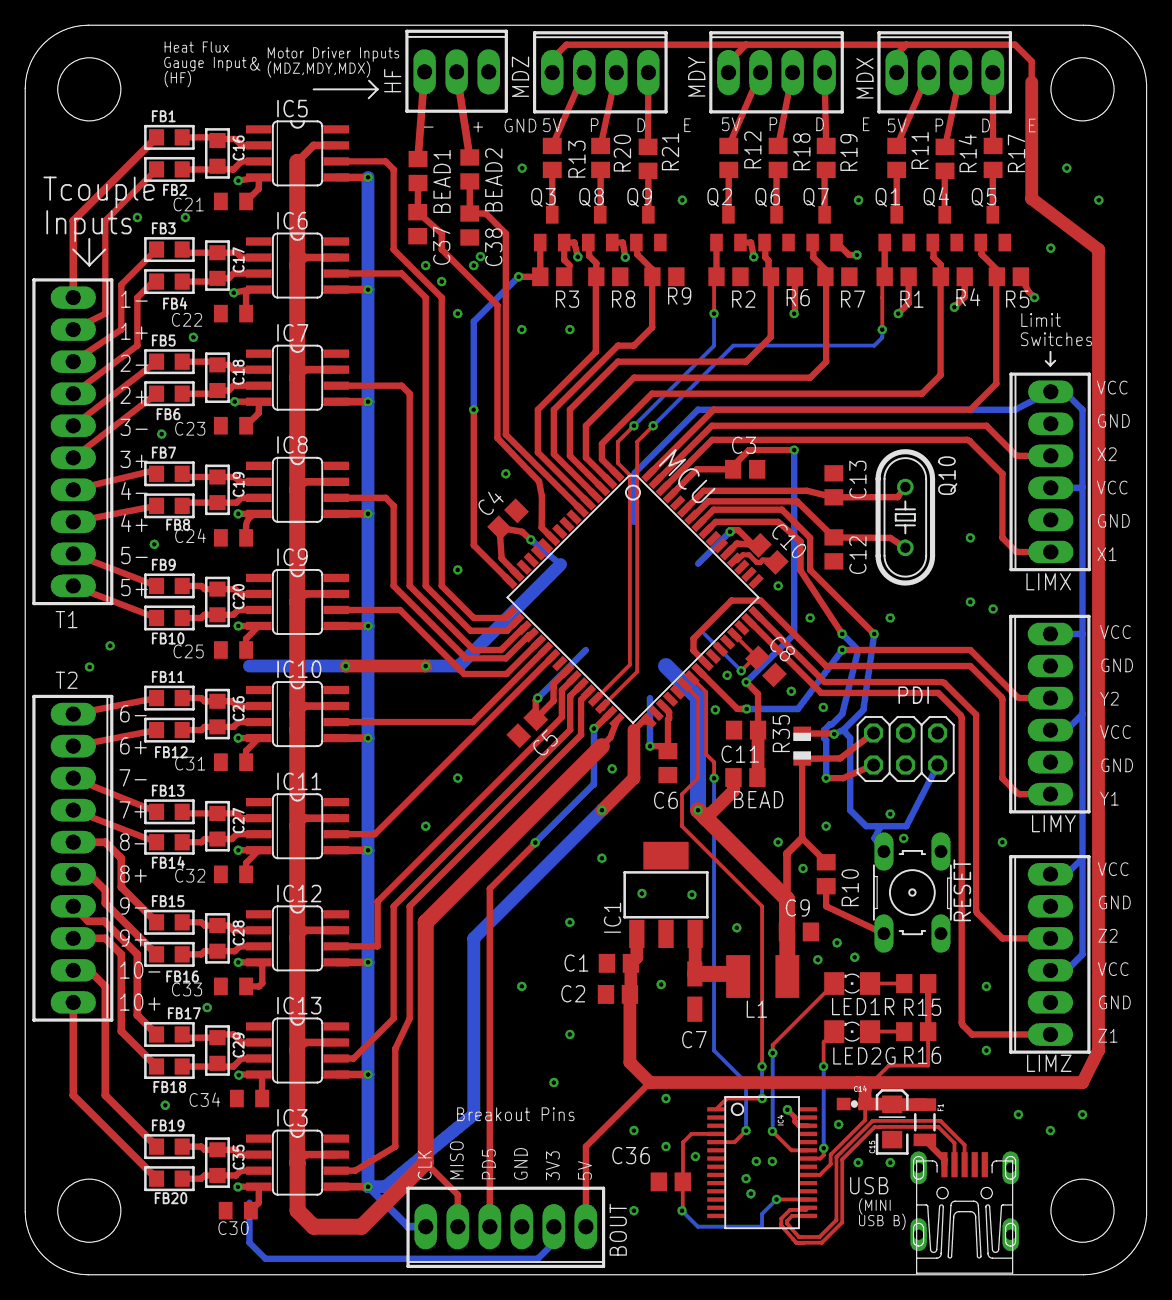
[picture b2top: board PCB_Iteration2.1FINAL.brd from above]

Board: 2 copper layers, 88.9 x 99.1 mm, 123 parts (0 on the bottom side), 111 nets.

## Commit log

2018-06-19 Updated all work from spring quarter

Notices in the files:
parts and their libraries:
SparkFun-Capacitors: Licensing: CC v3.0 Share-Alike You are welcome to use this library for commercial purposes.
